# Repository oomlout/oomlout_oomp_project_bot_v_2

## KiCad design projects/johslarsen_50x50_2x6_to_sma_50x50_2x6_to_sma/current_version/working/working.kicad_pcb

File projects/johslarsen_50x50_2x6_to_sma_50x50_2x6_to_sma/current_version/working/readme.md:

# 50x50_2x6_to_sma
 
## summary 
* id: johslarsen_50x50_2x6_to_sma_50x50_2x6_to_sma
* user: johslarsen
* name: 50x50_2x6_to_sma
* board: 50x50_2x6_to_sma
* repo: https://github.com/johslarsen/50x50_2x6_to_sma
* src_file_repo_kicad_pcb: 50x50_2x6_to_sma.kicad_pcb
* src_file_repo_kicad_pcb_link: https://github.com/johslarsen/50x50_2x6_to_sma/tree/master/50x50_2x6_to_sma.kicad_pcb

* src_file_repo_sch: 50x50_2x6_to_sma.sch
* src_file_repo_sch_link: https://github.com/johslarsen/50x50_2x6_to_sma/tree/master/50x50_2x6_to_sma.sch
* full details link: https://github.com/oomlout/oomlout_oomp_project_bot_v_2/tree/main/projects/johslarsen_50x50_2x6_to_sma_50x50_2x6_to_sma/current_version/working

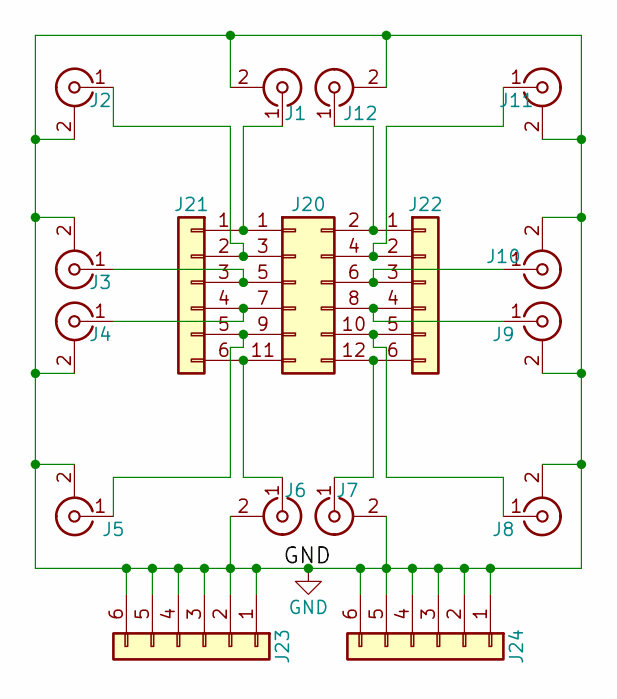
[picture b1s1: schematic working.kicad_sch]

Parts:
J1, J2, J3, J4, J5, J6, J7, J8, J9, J10, J11, J12: Conn_Coaxial; SMA_Board_Edge
J20: Conn_02x06_Counter_Clockwise; Pin_Header_Straight_2x06_Pitch2.54mm
J21, J22: Conn_01x06; Pin_Header_Straight_1x06_Pitch2.54mm
J23, J24: Conn_01x06; Edge_1x06

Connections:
GND: J1.2 (Ext), J2.2 (Ext), J3.2 (Ext), J4.2 (Ext), J5.2 (Ext), J6.2 (Ext), J7.2 (Ext), J8.2 (Ext), J9.2 (Ext), J10.2 (Ext), J11.2 (Ext), J12.2 (Ext), J23.1, J23.2, J23.3, J23.4, J23.5, J23.6, J24.1, J24.2, J24.3, J24.4, J24.5, J24.6
unnamed: J1.1 (In), J20.1, J21.1
unnamed: J2.1 (In), J20.3, J21.2
unnamed: J10.1 (In), J20.6, J22.3
unnamed: J11.1 (In), J20.4, J22.2
unnamed: J12.1 (In), J20.2, J22.1
unnamed: J3.1 (In), J20.5, J21.3
unnamed: J4.1 (In), J20.7, J21.4
unnamed: J9.1 (In), J20.8, J22.4
unnamed: J5.1 (In), J20.9, J21.5
unnamed: J8.1 (In), J20.10, J22.5
unnamed: J6.1 (In), J20.11, J21.6
unnamed: J7.1 (In), J20.12, J22.6

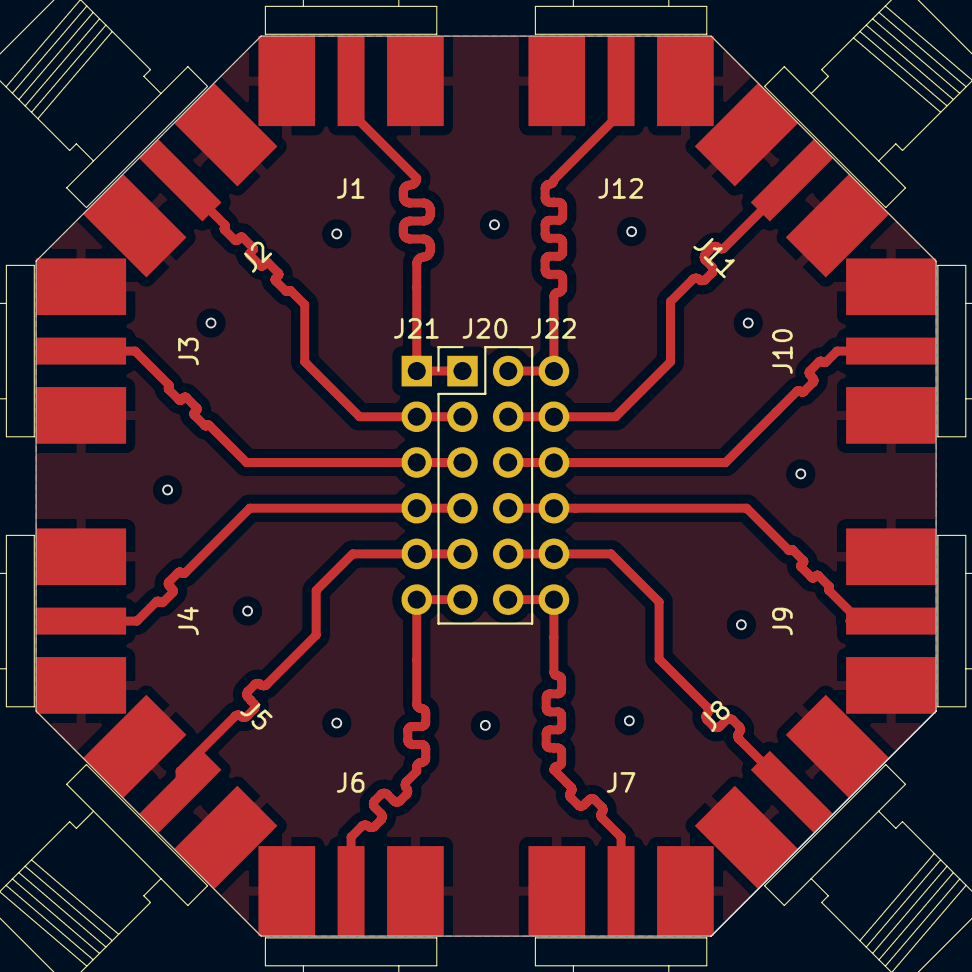
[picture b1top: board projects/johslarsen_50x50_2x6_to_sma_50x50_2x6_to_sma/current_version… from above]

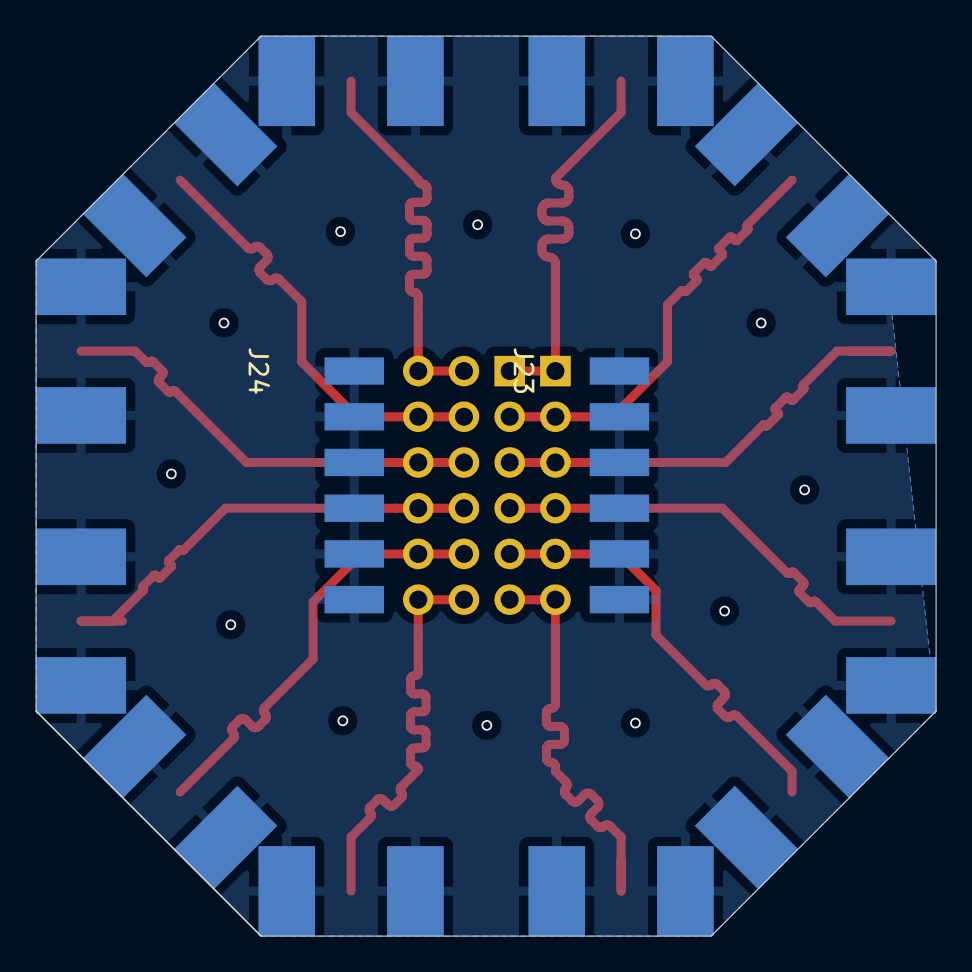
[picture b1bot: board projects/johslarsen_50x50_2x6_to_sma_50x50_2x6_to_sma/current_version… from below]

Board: 2 copper layers, 50.0 x 50.0 mm, 17 parts (2 on the bottom side), 13 nets.

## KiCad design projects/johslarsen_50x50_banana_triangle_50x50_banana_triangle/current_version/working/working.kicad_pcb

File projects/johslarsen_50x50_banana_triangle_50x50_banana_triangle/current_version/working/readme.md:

# 50x50_banana_triangle
 
## summary 
* id: johslarsen_50x50_banana_triangle_50x50_banana_triangle
* user: johslarsen
* name: 50x50_banana_triangle
* board: 50x50_banana_triangle
* repo: https://github.com/johslarsen/50x50_banana_triangle
* src_file_repo_kicad_pcb: 50x50_banana_triangle.kicad_pcb
* src_file_repo_kicad_pcb_link: https://github.com/johslarsen/50x50_banana_triangle/tree/master/50x50_banana_triangle.kicad_pcb

* src_file_repo_sch: 50x50_banana_triangle.sch
* src_file_repo_sch_link: https://github.com/johslarsen/50x50_banana_triangle/tree/master/50x50_banana_triangle.sch
* full details link: https://github.com/oomlout/oomlout_oomp_project_bot_v_2/tree/main/projects/johslarsen_50x50_banana_triangle_50x50_banana_triangle/current_version/working

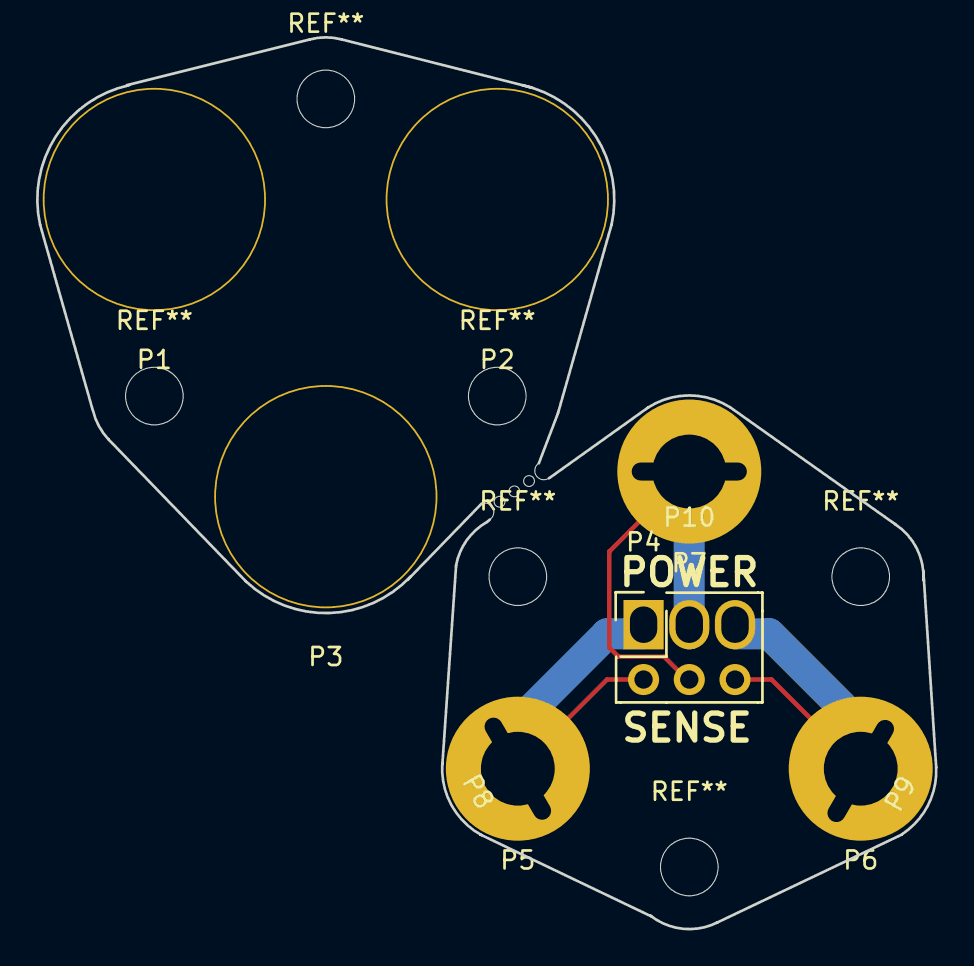
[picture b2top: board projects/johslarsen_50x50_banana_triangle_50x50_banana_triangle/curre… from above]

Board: 2 copper layers, 49.9 x 49.5 mm, 11 parts (0 on the bottom side), 3 nets.

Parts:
Mouse_Bites_3_1mm: VAL**; Mouse_Bites_3_1mm
P1, P2, P3: CONN_01X01; Banana_Socket_Shrouded_Multi-Conntact_SLB4
P4: CONN_02X03; Socket_Strip_Straight_2x03
P5, P6, P7: CONN_01X01; Banana_Plug_Friction_Fit
P8, P9, P10: CONN_01X01; Spade_6.3mm

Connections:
unnamed: P4.1, P4.2, P5.1, P8.1
unnamed: P4.5, P4.6, P6.1, P9.1
unnamed: P4.3, P4.4, P7.1, P10.1

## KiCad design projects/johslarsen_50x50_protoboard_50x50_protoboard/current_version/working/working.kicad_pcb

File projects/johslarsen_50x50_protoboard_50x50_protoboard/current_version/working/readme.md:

# 50x50_protoboard
 
## summary 
* id: johslarsen_50x50_protoboard_50x50_protoboard
* user: johslarsen
* name: 50x50_protoboard
* board: 50x50_protoboard
* repo: https://github.com/johslarsen/50x50_protoboard
* src_file_repo_kicad_pcb: 50x50_protoboard.kicad_pcb
* src_file_repo_kicad_pcb_link: https://github.com/johslarsen/50x50_protoboard/tree/master/50x50_protoboard.kicad_pcb

* src_file_repo_sch: 50x50_protoboard.sch
* src_file_repo_sch_link: https://github.com/johslarsen/50x50_protoboard/tree/master/50x50_protoboard.sch
* full details link: https://github.com/oomlout/oomlout_oomp_project_bot_v_2/tree/main/projects/johslarsen_50x50_protoboard_50x50_protoboard/current_version/working

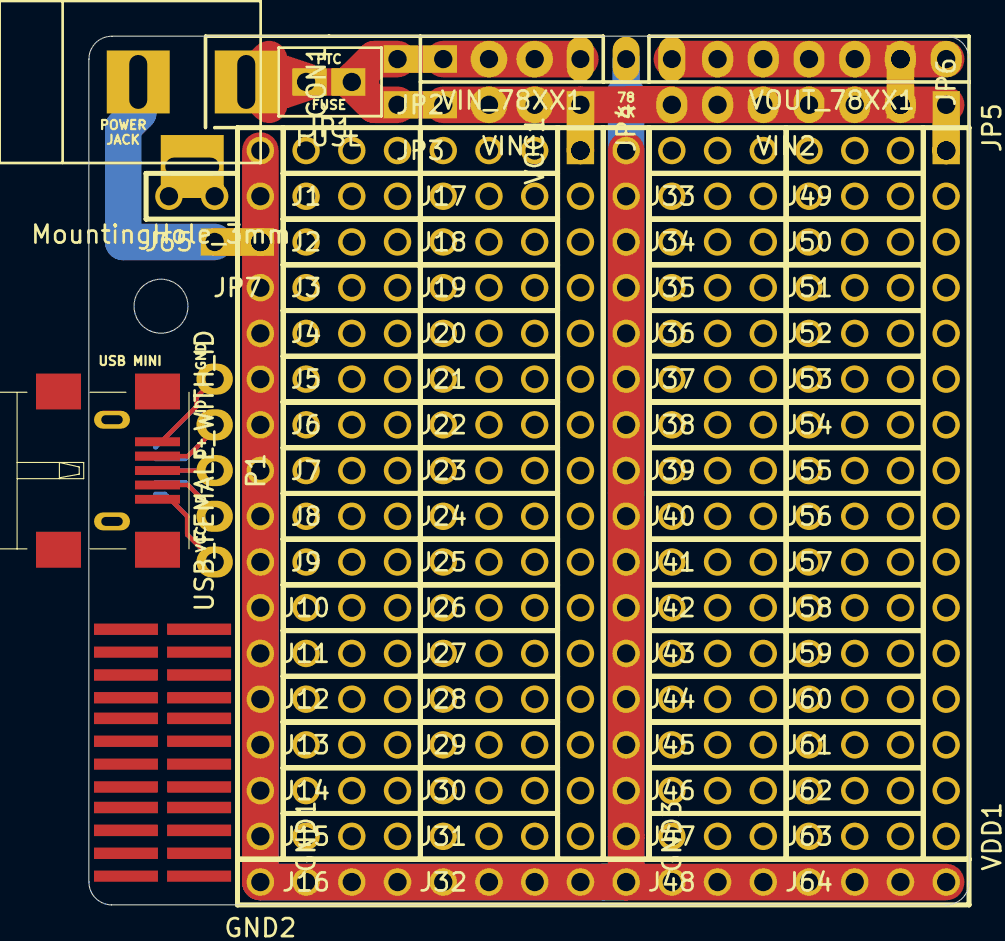
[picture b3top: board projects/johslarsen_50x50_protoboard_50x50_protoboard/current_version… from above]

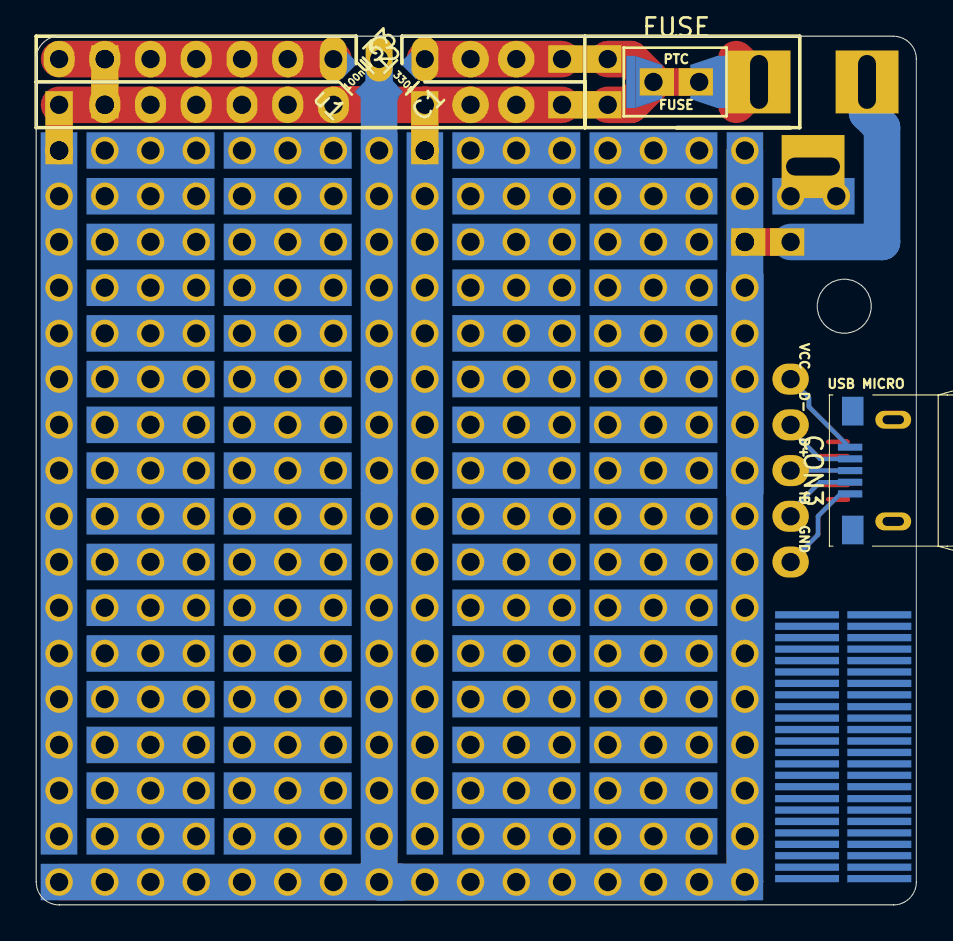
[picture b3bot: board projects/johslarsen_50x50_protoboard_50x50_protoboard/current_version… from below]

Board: 2 copper layers, 48.9 x 48.3 mm, 97 parts (7 on the bottom side), 15 nets.

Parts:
C1: u33; C_0805_HandSoldering
C2: u1; C_0805_HandSoldering
CON1: BARREL_JACK
CON2: USB_FEMALE_WITH_ID; USB_Mini-B_Female
CON3: USB_FEMALE_WITH_ID; USB_Micro-B_Female_Wellco_AUSB_1011_05S2
F1, F2: FUSE; CC12ZZ
GND1, GND2, GND3: INTERCONNECT_16X1; Interconnect_1x16
J1, J2, J3, J4, J5, J6, J7, J8, J9, J10, J11, J12, J13, J14, J15, J16, J17, J18, J19, J20, J21, J22, J23, J24, J25, J26, J27, J28, J29, J30, J31, J32, J33, J34, J35, J36, J37, J38, J39, J40, J41, J42, J43, J44, J45, J46, J47, J48, J49, J50, J51, J52, J53, J54, J55, J56, J57, J58, J59, J60, J61, J62, J63, J64: INTERCONNECT_3X1; Interconnect_1x03
J65: INTERCONNECT_2X1; Interconnect_1x02
JP1, JP2, JP3, JP4, JP5, JP6, JP7: JUMPER; Solder_Jumper_1x2_Shorted_T
MountingHole_3mm: VAL**; MountingHole_3mm
P1: CONN_5; Pin_Header_Straight_1x05
Ref**: Val**; SMD_127_357_4X2
Ref**#2, Ref**#3: Val**; SMD_127_357_4X2
Ref**#4, Ref**#5, Ref**#6: Val**; SMD_065_357_8X2
U1: LM7805CT; TO-220_Neutral123_Vertical
VCC1: INTERCONNECT_16X1; Interconnect_1x16
VDD1: INTERCONNECT_16X1; Interconnect_1x16
VIN1: CONN_2; Socket_Strip_Straight_1x02
VIN2: CONN_6; Socket_Strip_Straight_1x06
VIN_78XX1: CONN_2; Socket_Strip_Straight_1x02
VOUT_78XX1: CONN_6; Socket_Strip_Straight_1x06

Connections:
unnamed: C1.1, JP2.2, U1.1, VIN_78XX1.1, VIN_78XX1.2
unnamed: C1.2, C2.2, GND1.1, GND2.1, GND3.1, JP7.2, U1.2
unnamed: C2.1, JP6.2, U1.3, VOUT_78XX1.1, VOUT_78XX1.2, VOUT_78XX1.3, VOUT_78XX1.4, VOUT_78XX1.5, VOUT_78XX1.6
unnamed: CON1.1, F1.1, F2.1, JP1.1
unnamed: CON1.2, JP7.1
unnamed: CON1.3, J65.1
unnamed: CON2.1, CON3.5, P1.1
unnamed: CON2.2, CON3.4, P1.2
unnamed: CON2.3, CON3.3, P1.3
unnamed: CON2.4, CON3.2, P1.4
unnamed: CON2.5, CON3.1, P1.5
unnamed: F1.2, F2.2, JP1.2, JP2.1, JP3.1
unnamed: JP3.2, JP4.2, JP5.2, JP6.1, VIN1.1, VIN1.2, VIN2.1, VIN2.2, VIN2.3, VIN2.4, VIN2.5, VIN2.6
unnamed: JP4.1, VCC1.1
unnamed: JP5.1, VDD1.1
